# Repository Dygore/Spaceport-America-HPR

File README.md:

# Oklahoma State University High Powered Rocketry Spaceport America

## About
This project will be used to create a working airbrake system for the Spaceport America Competition in June. The goal of this competition is to get as close to 10,000 feet as possible with a High Powered Rocket.

Our airbrake will be controlled by stepper motors with a gear increase for torque, which will turn a lead screw after the rocket motor has burnt out until apogee. The STM32 Board will receive telemetry data over SPI from the Telemega, it will access a lookup table on our flash chip to get the corresponding drag coefficients. It will then drive the stepper motor using a stepper motor controller to step the airbrake pads out, thus slowing down the rocket. This could be further enhanced using more accurate data and a PID controller.

## Details
The code will be written in two main sections
Section 1: STM32 code written in STM32 CubeIDE programmed using SWD pins
Section 2: Code written and built in Linux using Altus Metrum's Telemega code as a base

## References
For more information on the Altus Metrum Telemega visit https://altusmetrum.org/

Thank you to Bdale Garbee for his help in the development process and for designing the Telemega https://gag.com/bdale/

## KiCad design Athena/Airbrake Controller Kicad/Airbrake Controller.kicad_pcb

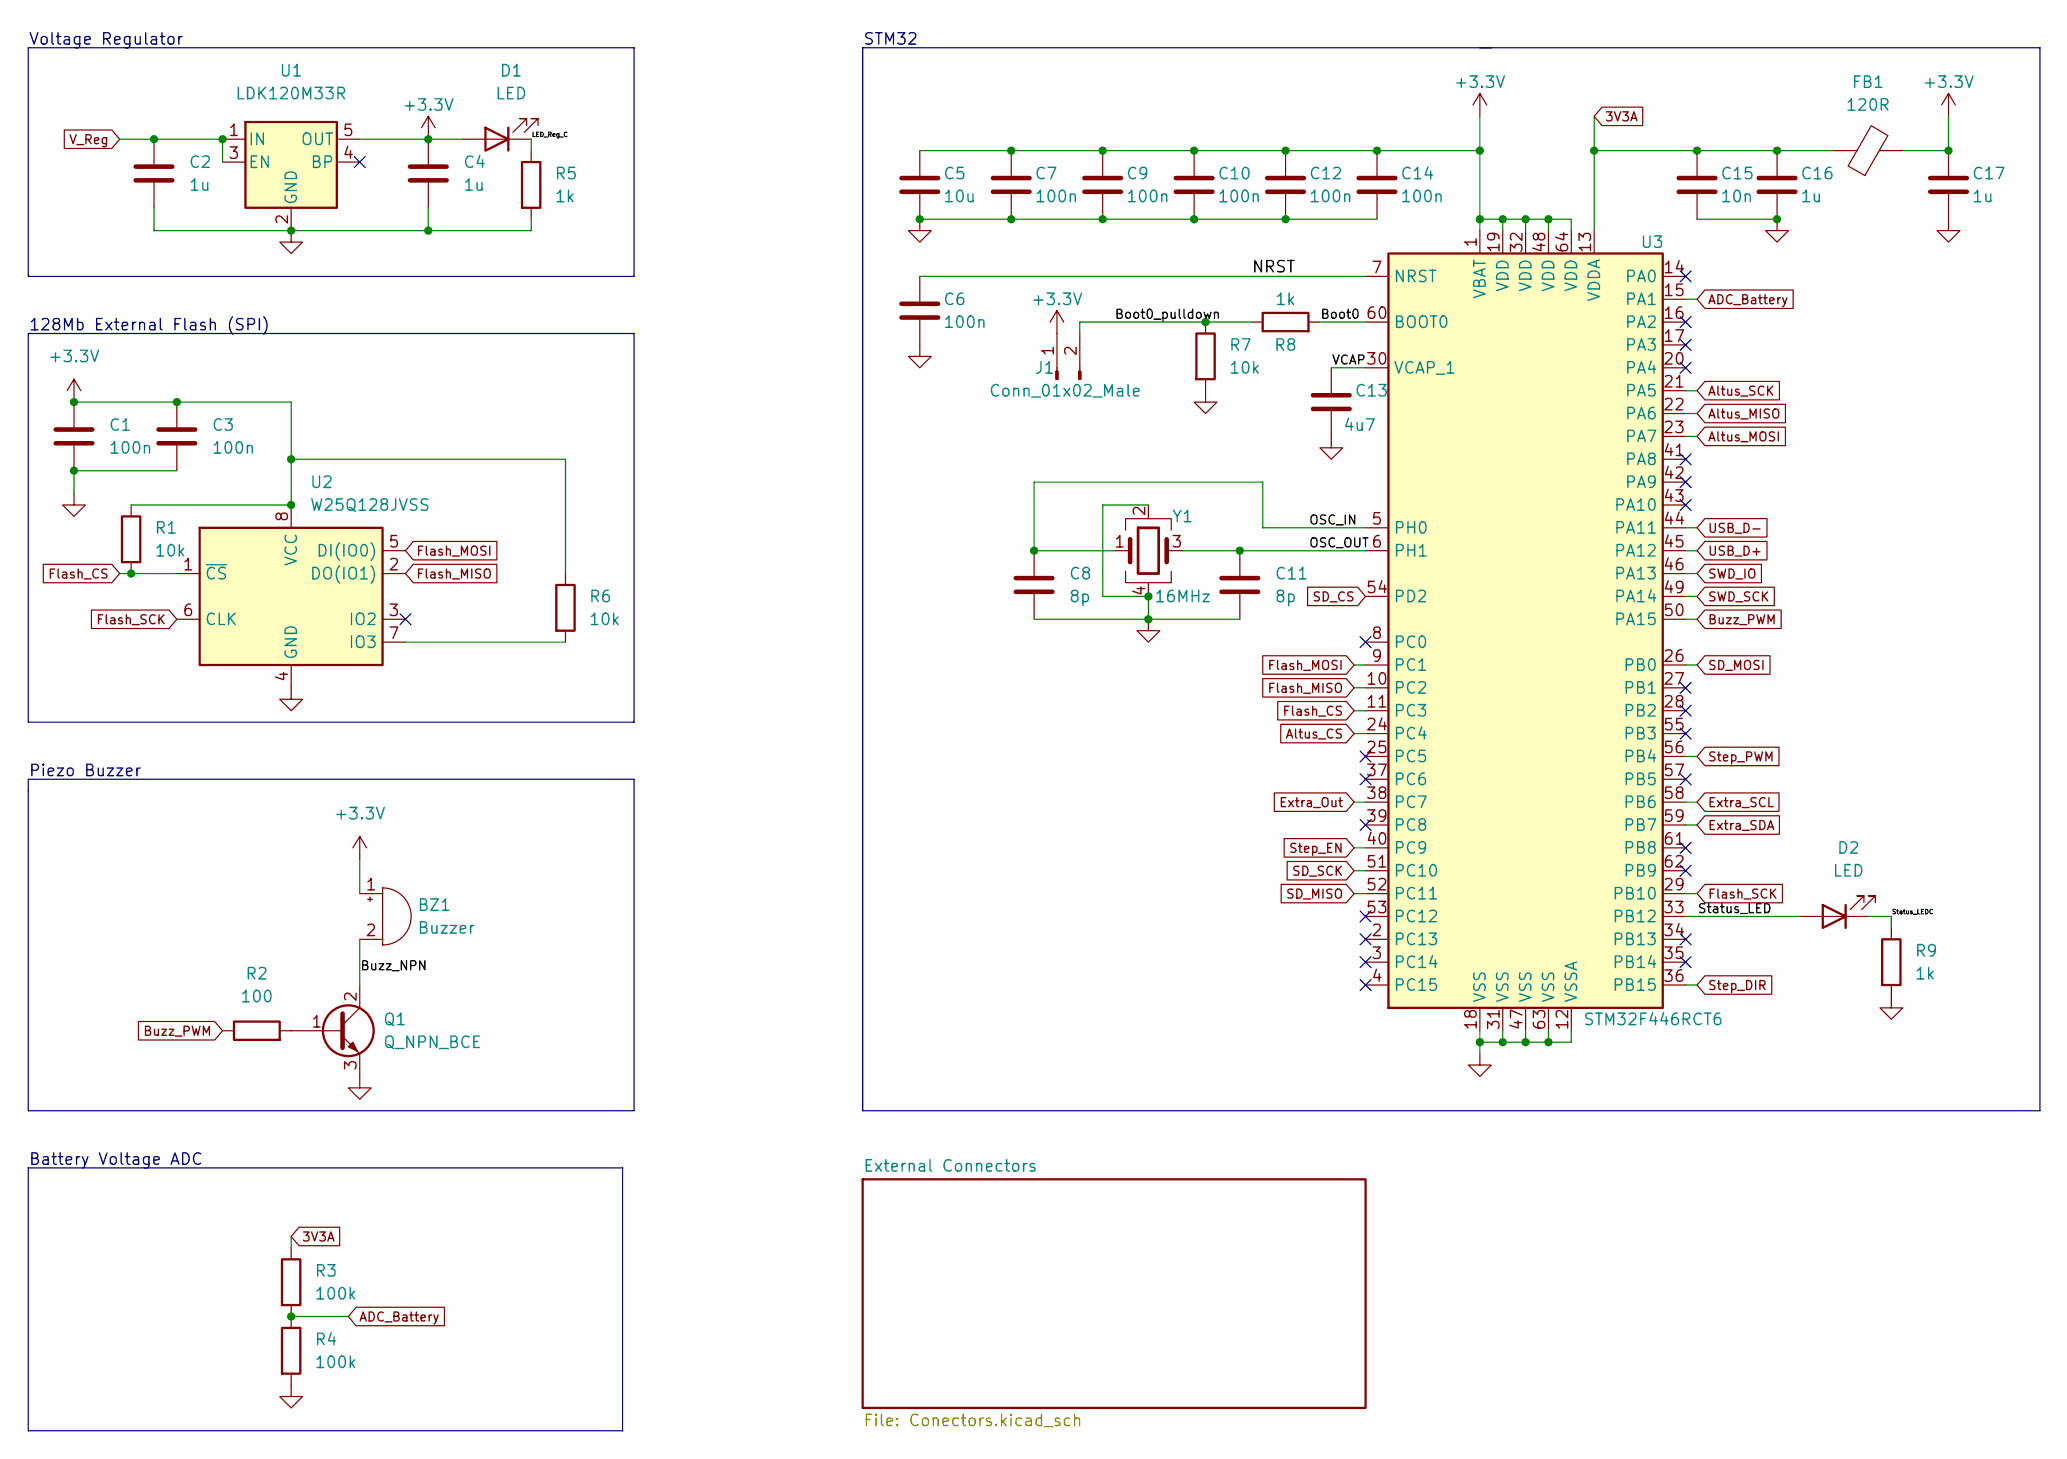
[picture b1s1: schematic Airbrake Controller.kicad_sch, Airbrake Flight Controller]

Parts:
BZ1: Buzzer; Buzzer_Murata_PKLCS1212E
C1, C3, C6, C7, C9, C10, C12, C14: 100n; C_0805_2012Metric
C2, C4, C16, C17: 1u; C_0805_2012Metric
C5: 10u; C_0805_2012Metric
C8, C11: 8p; C_0805_2012Metric
C13: 4u7; C_0805_2012Metric
C15: 10n; C_0805_2012Metric
D1, D2: LED; LED_0805_2012Metric
FB1: 120R; R_0805_2012Metric_Pad1.20x1.40mm_HandSolder
J1: Conn_01x02_Male; PinHeader_2x01_P2.54mm_Vertical
Q1: Q_NPN_BCE; SOT-23
R1, R6, R7: 10k; R_0805_2012Metric
R2: 100; R_0805_2012Metric
R3, R4: 100k; R_0805_2012Metric
R5, R8, R9: 1k; R_0805_2012Metric
U1: LDK120M33R; SOT-23-5
U2: W25Q128JVSS; SOIC-8_5.23x5.23mm_P1.27mm
U3: STM32F446RCT6; LQFP-64_10x10mm_P0.5mm
Y1: 16MHz; Crystal_SMD_3225-4Pin_3.2x2.5mm

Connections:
3V3A: C15.1, C16.1, FB1.1, R3.1, U3.13 (VDDA)
+3V3: BZ1.1 (-), C1.1, C3.1, C4.1, C5.1, C7.1, C9.1, C10.1, C12.1, C14.1, C17.1, D1.2 (A), FB1.2, J1.1, R1.1, R6.1, U1.5 (OUT), U2.8 (VCC), U3.1 (VBAT), U3.19 (VDD), U3.32 (VDD), U3.48 (VDD), U3.64 (VDD); also elsewhere on the board
/Boot0: R8.2, U3.60 (BOOT0)
/Boot0_pulldown: J1.2, R7.1, R8.1
/Buzz_NPN: BZ1.2 (+), Q1.2 (C)
/LED_Reg_C: D1.1 (K), R5.1
/NRST: C6.1, U3.7 (NRST)
/OSC_IN: C8.1, U3.5 (PH0), Y1.1
/OSC_OUT: C11.1, U3.6 (PH1), Y1.3
/Status_LED: D2.2 (A), U3.33 (PB12)
/Status_LEDC: D2.1 (K), R9.1
/VCAP: C13.1, U3.30 (VCAP_1)
ADC_Battery: R3.2, R4.1, U3.15 (PA1)
Altus_CS: U3.24 (PC4); also elsewhere on the board
Altus_MISO: U3.22 (PA6); also elsewhere on the board
Altus_MOSI: U3.23 (PA7); also elsewhere on the board
Altus_SCK: U3.21 (PA5); also elsewhere on the board
Buzz_PWM: R2.1, U3.50 (PA15)
Extra_Out: U3.38 (PC7); also elsewhere on the board
Extra_SCL: U3.58 (PB6); also elsewhere on the board
Extra_SDA: U3.59 (PB7); also elsewhere on the board
Flash_CS: R1.2, U2.1 (~CS), U3.11 (PC3)
Flash_MISO: U2.2 (DO(IO1)), U3.10 (PC2)
Flash_MOSI: U2.5 (DI(IO0)), U3.9 (PC1)
Flash_SCK: U2.6 (CLK), U3.29 (PB10)
GND: C1.2, C2.2, C3.2, C4.2, C5.2, C6.2, C7.2, C8.2, C9.2, C10.2, C11.2, C12.2, C13.2, C14.2, C15.2, C16.2, C17.2, Q1.3 (E), R4.2, R5.2, R7.2, R9.2, U1.2 (GND), U2.4 (GND), U3.12 (VSSA), U3.18 (VSS), U3.31 (VSS), U3.47 (VSS), U3.63 (VSS), Y1.2, Y1.4; also elsewhere on the board
unnamed: Q1.1 (B), R2.2
unnamed: R6.2, U2.7 (IO3)
SD_CS: U3.54 (PD2); also elsewhere on the board
SD_MISO: U3.52 (PC11); also elsewhere on the board
SD_MOSI: U3.26 (PB0); also elsewhere on the board
SD_SCK: U3.51 (PC10); also elsewhere on the board
SWD_IO: U3.46 (PA13); also elsewhere on the board
SWD_SCK: U3.49 (PA14); also elsewhere on the board
Step_DIR: U3.36 (PB15); also elsewhere on the board
Step_EN: U3.40 (PC9); also elsewhere on the board
Step_PWM: U3.56 (PB4); also elsewhere on the board
USB_D+: U3.45 (PA12); also elsewhere on the board
USB_D-: U3.44 (PA11); also elsewhere on the board
V_Reg: C2.1, U1.1 (IN), U1.3 (EN); also elsewhere on the board

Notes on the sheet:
Voltage Regulator
128Mb External Flash (SPI)
Piezo Buzzer
Battery Voltage ADC
STM32

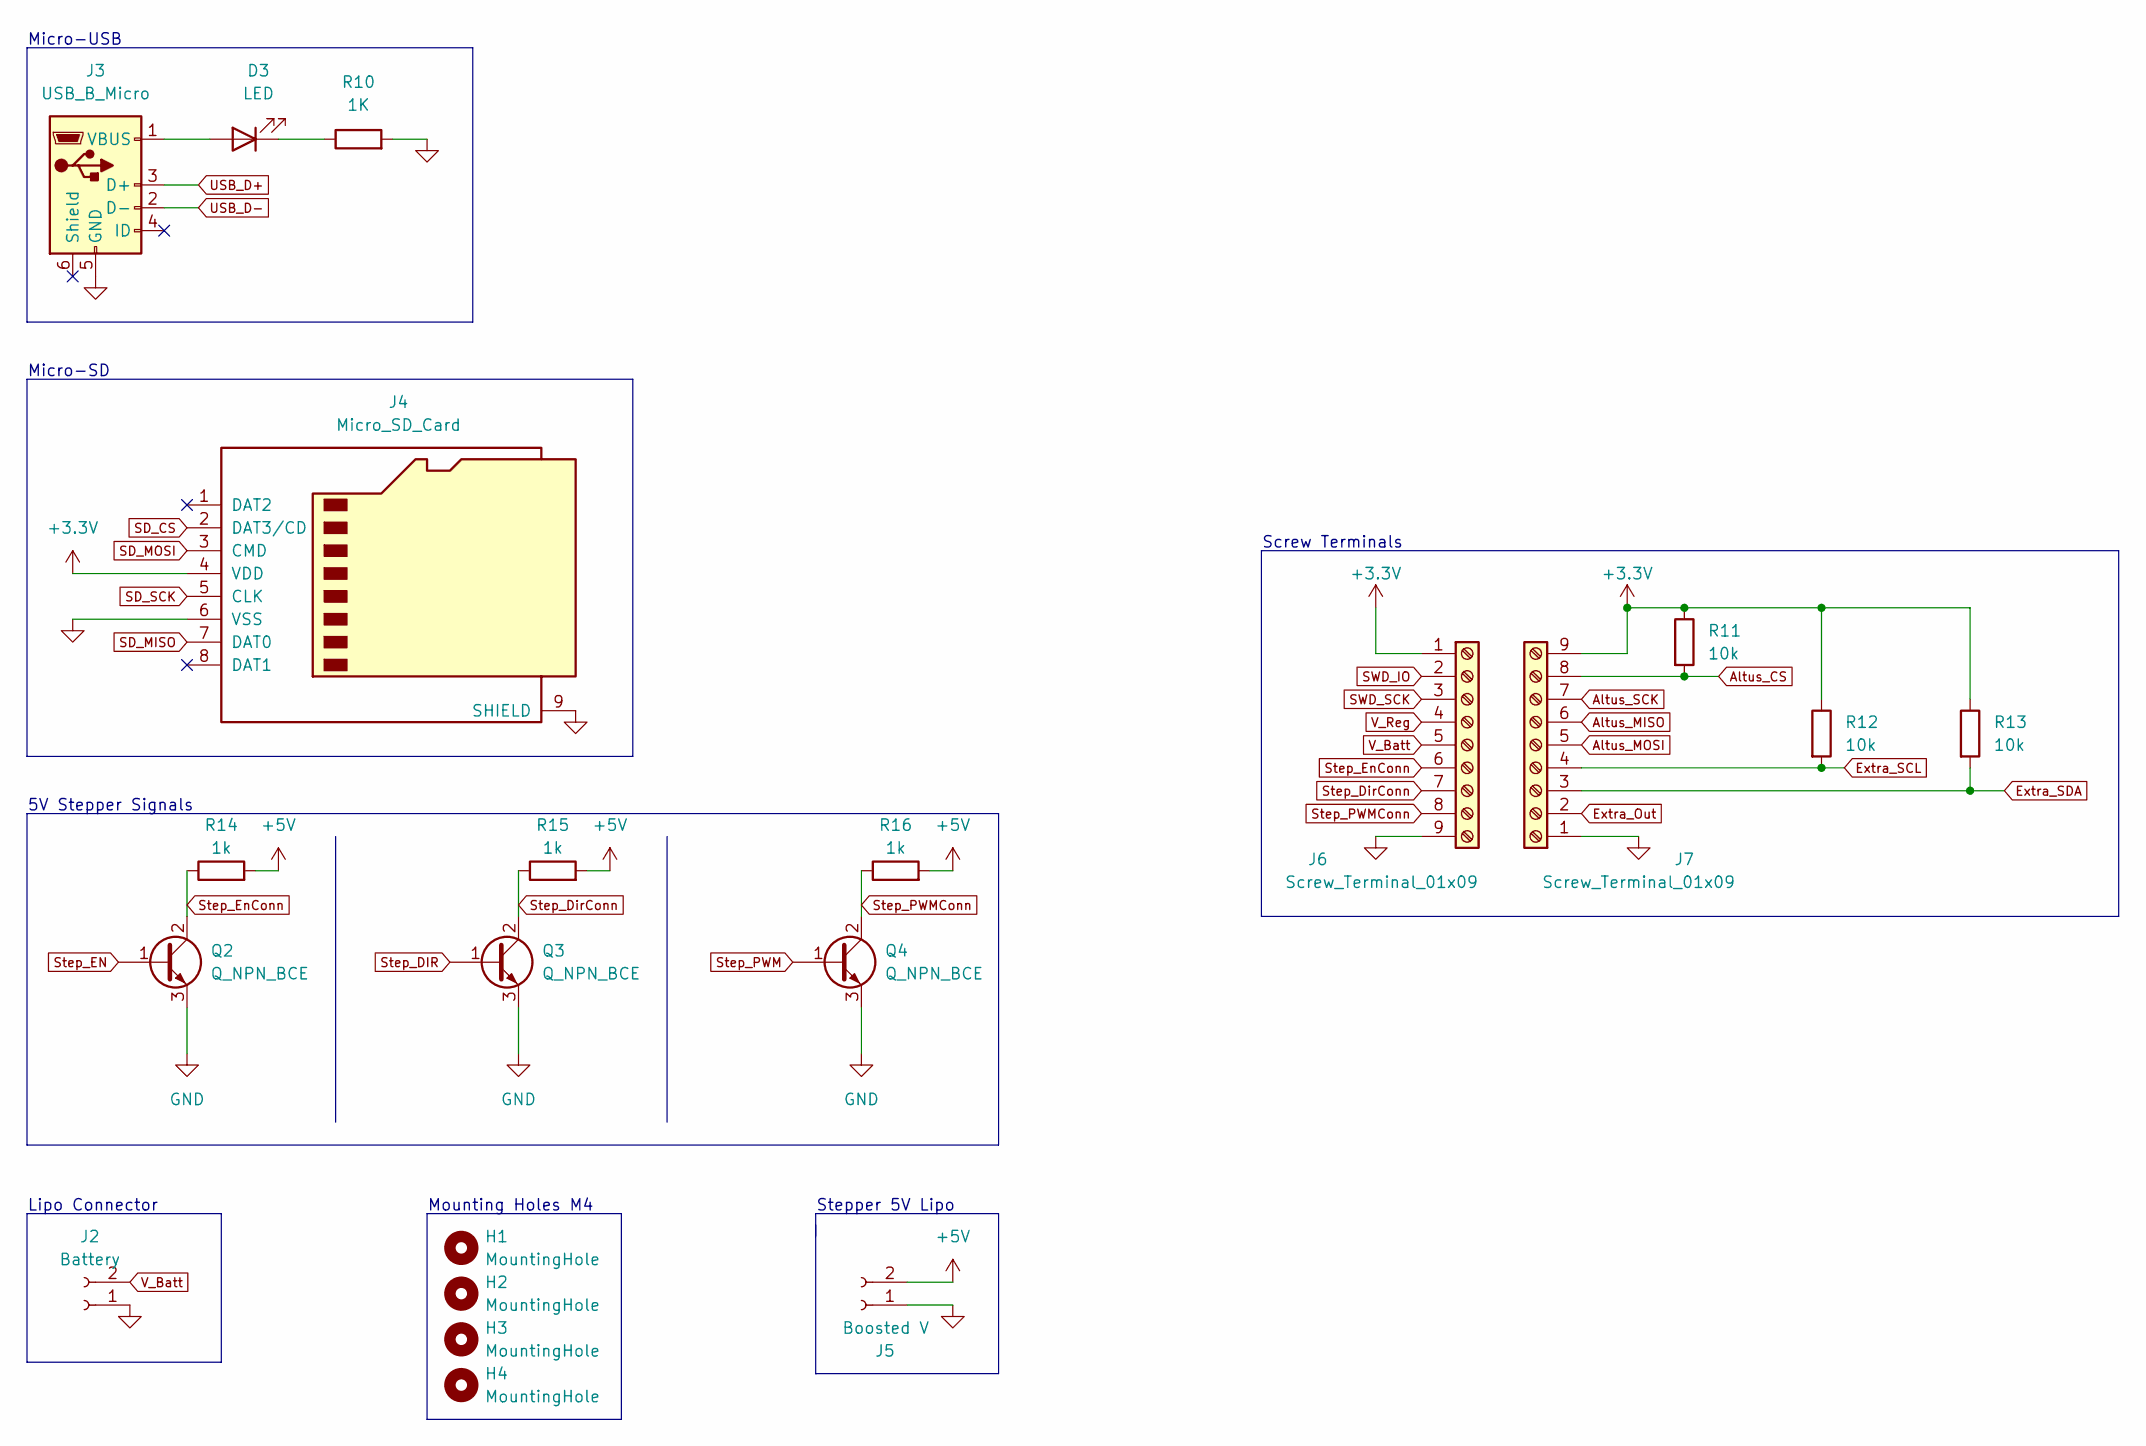
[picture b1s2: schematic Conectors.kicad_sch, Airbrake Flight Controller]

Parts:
D3: LED; LED_0805_2012Metric
H1, H2, H4: MountingHole; MountingHole_3.2mm_M3_Pad_Via
H3: MountingHole; MountingHole_3mm_Pad_Via
J2: Battery; JST_PH_B2B-PH-K_1x02_P2.00mm_Vertical
J3: USB_B_Micro; USB_Micro-B_Amphenol_10118194_Horizontal
J4: Micro_SD_Card; microSD_HC_Molex_104031-0811
J5: Boosted V; TerminalBlock_4Ucon_1x02_P3.50mm_Horizontal
J6, J7: Screw_Terminal_01x09; TerminalBlock_4Ucon_1x09_P3.50mm_Horizontal
Q2, Q3, Q4: Q_NPN_BCE; SOT-23
R10: 1K; R_0805_2012Metric
R11, R12, R13: 10k; R_0805_2012Metric
R14, R15, R16: 1k; R_0805_2012Metric

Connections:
+3V3: J4.4 (VDD), J6.1, J7.9, R11.1, R12.1, R13.1; also elsewhere on the board
+5V: J5.2, R14.2, R15.2, R16.2
Altus_CS: J7.8, R11.2; also elsewhere on the board
Altus_MISO: J7.6; also elsewhere on the board
Altus_MOSI: J7.5; also elsewhere on the board
Altus_SCK: J7.7; also elsewhere on the board
Extra_Out: J7.2; also elsewhere on the board
Extra_SCL: J7.4, R12.2; also elsewhere on the board
Extra_SDA: J7.3, R13.2; also elsewhere on the board
GND: J2.1, J3.5 (GND), J4.6 (VSS), J4.9 (SHIELD), J5.1, J6.9, J7.1, Q2.3 (E), Q3.3 (E), Q4.3 (E), R10.2; also elsewhere on the board
unnamed: D3.1 (K), R10.1
unnamed: D3.2 (A), J3.1 (VBUS)
SD_CS: J4.2 (DAT3/CD); also elsewhere on the board
SD_MISO: J4.7 (DAT0); also elsewhere on the board
SD_MOSI: J4.3 (CMD); also elsewhere on the board
SD_SCK: J4.5 (CLK); also elsewhere on the board
SWD_IO: J6.2; also elsewhere on the board
SWD_SCK: J6.3; also elsewhere on the board
Step_DIR: Q3.1 (B); also elsewhere on the board
Step_DirConn: J6.7, Q3.2 (C), R15.1
Step_EN: Q2.1 (B); also elsewhere on the board
Step_EnConn: J6.6, Q2.2 (C), R14.1
Step_PWM: Q4.1 (B); also elsewhere on the board
Step_PWMConn: J6.8, Q4.2 (C), R16.1
USB_D+: J3.3 (D+); also elsewhere on the board
USB_D-: J3.2 (D-); also elsewhere on the board
V_Batt: J2.2, J6.5
V_Reg: J6.4; also elsewhere on the board

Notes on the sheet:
Micro-USB
5V Stepper Signals
Lipo Connector
Stepper 5V Lipo
Screw Terminals
Micro-SD
Mounting Holes M4

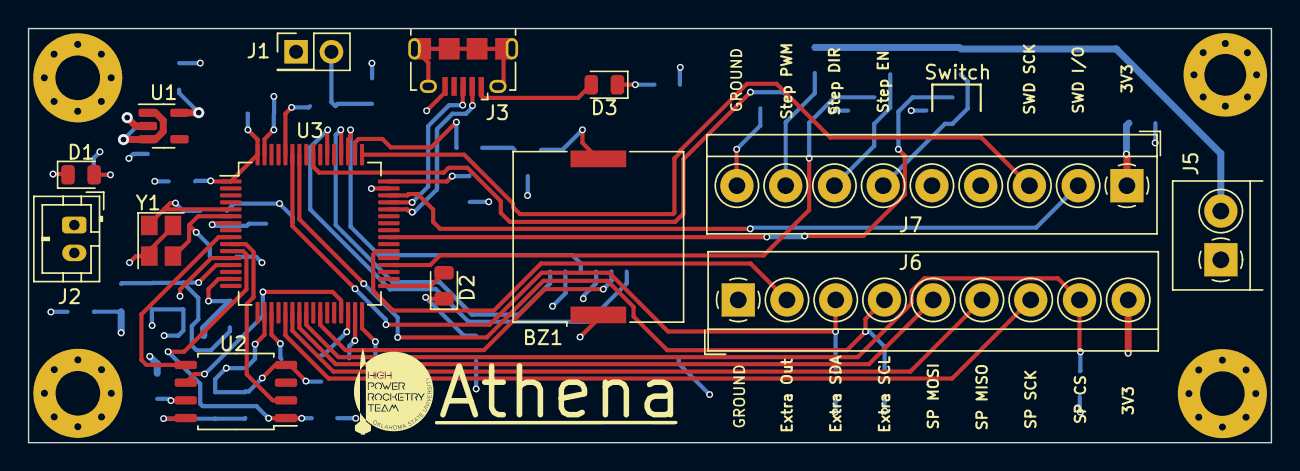
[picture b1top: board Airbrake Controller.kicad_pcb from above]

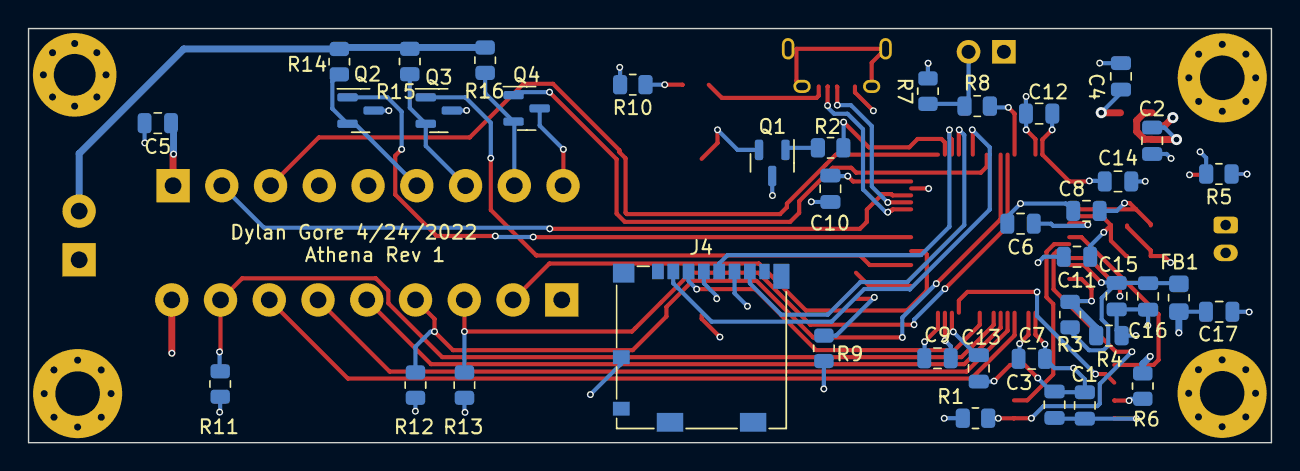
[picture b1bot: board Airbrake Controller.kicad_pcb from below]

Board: 4 copper layers, 89.2 x 29.7 mm, 57 parts (39 on the bottom side), 47 nets.

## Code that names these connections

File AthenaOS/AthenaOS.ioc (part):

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Mcu.Name=STM32F446R(C-E)Tx
Mcu.Package=LQFP64
Mcu.UserName=STM32F446RCTx
PA1.GPIOParameters=GPIO_Label
PA1.GPIO_Label=ADC_Batt
PA1.Signal=ADCx_IN1
PA11.GPIOParameters=GPIO_Label
PA11.GPIO_Label=USB-
PA11.Mode=Device_Only
PA11.Signal=USB_OTG_FS_DM
PA12.GPIOParameters=GPIO_Label
PA12.GPIO_Label=USB+
PA12.Mode=Device_Only
PA12.Signal=USB_OTG_FS_DP
PA13.Mode=Serial_Wire
PA13.Signal=SYS_JTMS-SWDIO
PA14.Mode=Serial_Wire
PA14.Signal=SYS_JTCK-SWCLK
PA15.GPIOParameters=GPIO_Speed,GPIO_PuPd,GPIO_Label,GPIO_ModeDefaultOutputPP
PA15.GPIO_Label=Buzz_PWM
PA15.GPIO_ModeDefaultOutputPP=GPIO_MODE_OUTPUT_PP
PA15.GPIO_PuPd=GPIO_NOPULL
PA15.GPIO_Speed=GPIO_SPEED_FREQ_HIGH
PA15.Signal=GPIO_Output
PA5.GPIOParameters=GPIO_Label
PA5.GPIO_Label=Altus_SCK
PA5.Mode=Full_Duplex_Slave
PA5.Signal=SPI1_SCK
PA6.GPIOParameters=GPIO_Label
PA6.GPIO_Label=Altus_MISO
PA6.Mode=Full_Duplex_Slave
PA6.Signal=SPI1_MISO
PA7.GPIOParameters=GPIO_Label
PA7.GPIO_Label=Altus_MOSI
PA7.Mode=Full_Duplex_Slave
PA7.Signal=SPI1_MOSI
PB0.GPIOParameters=GPIO_Label
PB0.GPIO_Label=SD_MOSI
PB0.Mode=Full_Duplex_Master
PB0.Signal=SPI3_MOSI
PB10.GPIOParameters=GPIO_Label
PB10.GPIO_Label=Flash_SCK
PB10.Mode=Full_Duplex_Master
PB10.Signal=SPI2_SCK
PB12.GPIOParameters=GPIO_Label
PB12.GPIO_Label=Status_LED
PB12.Signal=GPIO_Output
PB15.GPIOParameters=GPIO_Label
PB15.GPIO_Label=Step_DIR
PB15.Signal=GPIO_Output
PB4.GPIOParameters=GPIO_Label
PB4.GPIO_Label=Step_PWM
PB4.Signal=GPIO_Output
PB6.GPIOParameters=GPIO_Label
PB6.GPIO_Label=Extra_SCL
PB6.Mode=I2C
PB6.Signal=I2C1_SCL
PB7.GPIOParameters=GPIO_Label
PB7.GPIO_Label=Extra_SDA
PB7.Mode=I2C
PB7.Signal=I2C1_SDA
PC1.GPIOParameters=GPIO_Label
PC1.GPIO_Label=Flash_MOSI
PC1.Mode=Full_Duplex_Master
PC1.Signal=SPI2_MOSI
PC10.GPIOParameters=GPIO_Label
PC10.GPIO_Label=SD_SCK
PC10.Mode=Full_Duplex_Master
PC10.Signal=SPI3_SCK
PC11.GPIOParameters=GPIO_Label
PC11.GPIO_Label=SD_MISO
PC11.Mode=Full_Duplex_Master
PC11.Signal=SPI3_MISO
PC2.GPIOParameters=GPIO_Label
PC2.GPIO_Label=Flash_MISO
PC2.Mode=Full_Duplex_Master
PC2.Signal=SPI2_MISO
PC3.GPIOParameters=GPIO_Label
PC3.GPIO_Label=Flash_CS
PC3.Signal=GPIO_Output
PC4.GPIOParameters=GPIO_Label
PC4.GPIO_Label=Altus_CS
PC4.Signal=GPIO_Input
PC7.GPIOParameters=GPIO_Label
PC7.GPIO_Label=Extra_out
PC7.Signal=GPIO_Output
PC9.GPIOParameters=GPIO_Label
PC9.GPIO_Label=Step_EN
PC9.Signal=GPIO_Output
PD2.GPIOParameters=GPIO_Label
PD2.GPIO_Label=SD_CS
PD2.Signal=GPIO_Output
PH0-OSC_IN.Mode=HSE-External-Oscillator
PH0-OSC_IN.Signal=RCC_OSC_IN
PH1-OSC_OUT.Mode=HSE-External-Oscillator
PH1-OSC_OUT.Signal=RCC_OSC_OUT
RCC.HSE_VALUE=16000000
RCC.SYSCLKFreq_VALUE=72000000
RCC.SYSCLKSource=RCC_SYSCLKSOURCE_PLLCLK
board=custom

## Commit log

2022-05-09 Adding Altos
2022-05-10 Altos
2022-05-10 Change File Name
2022-05-10 Move BOM
2022-05-10 AthenaOS
2022-05-10 AthenaOS: Stepper/Status LED
2022-05-16 Startup
2022-06-07 Flash Chip Driver
